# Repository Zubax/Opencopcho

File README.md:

# Opencopcho

Open hardware shield for the [NUCLEO-H743ZI](https://www.st.com/en/evaluation-tools/nucleo-h743zi.html) board
for UAVCAN development.

Ask questions on the [UAVCAN forum](https://forum.uavcan.org) or [Zubax forum](https://forum.zubax.com).

Opencopcho is pronounced like [*open-cop-chow*](https://translate.google.com/#en/en/opencopcho).

## Design

The shield features two CAN FD interfaces with three pairs of standard UAVCAN-compatible connectors
(two connectors per interface).

The shield can be assembled in two configurations: **full** and **micro**.
The full configuration provides three types of connectors defined by the UAVCAN specification:

* UAVCAN Micro type (JST GH 4-pin)
* UAVCAN D-Subminiature (D-Sub DE9, de-facto industry-standard CAN connector)
* 2.54mm pin headers for connection to panel-mounted UAVCAN M8 connectors
(M8 5-pin B-coded connector, also used in CANopen)

The micro configuration has only the UAVCAN Micro connectors populated.
In this configuration, Opencopcho can be used with other shields stacked on top of it.

Full configuration                  | Micro configuration
------------------------------------|------------------------------------------
     | 
  |

A 3D render is available here: <https://a360.co/2R1n94m>.

## License

This work is licensed under a
[Creative Commons Attribution 4.0 International License](http://creativecommons.org/licenses/by/4.0/).

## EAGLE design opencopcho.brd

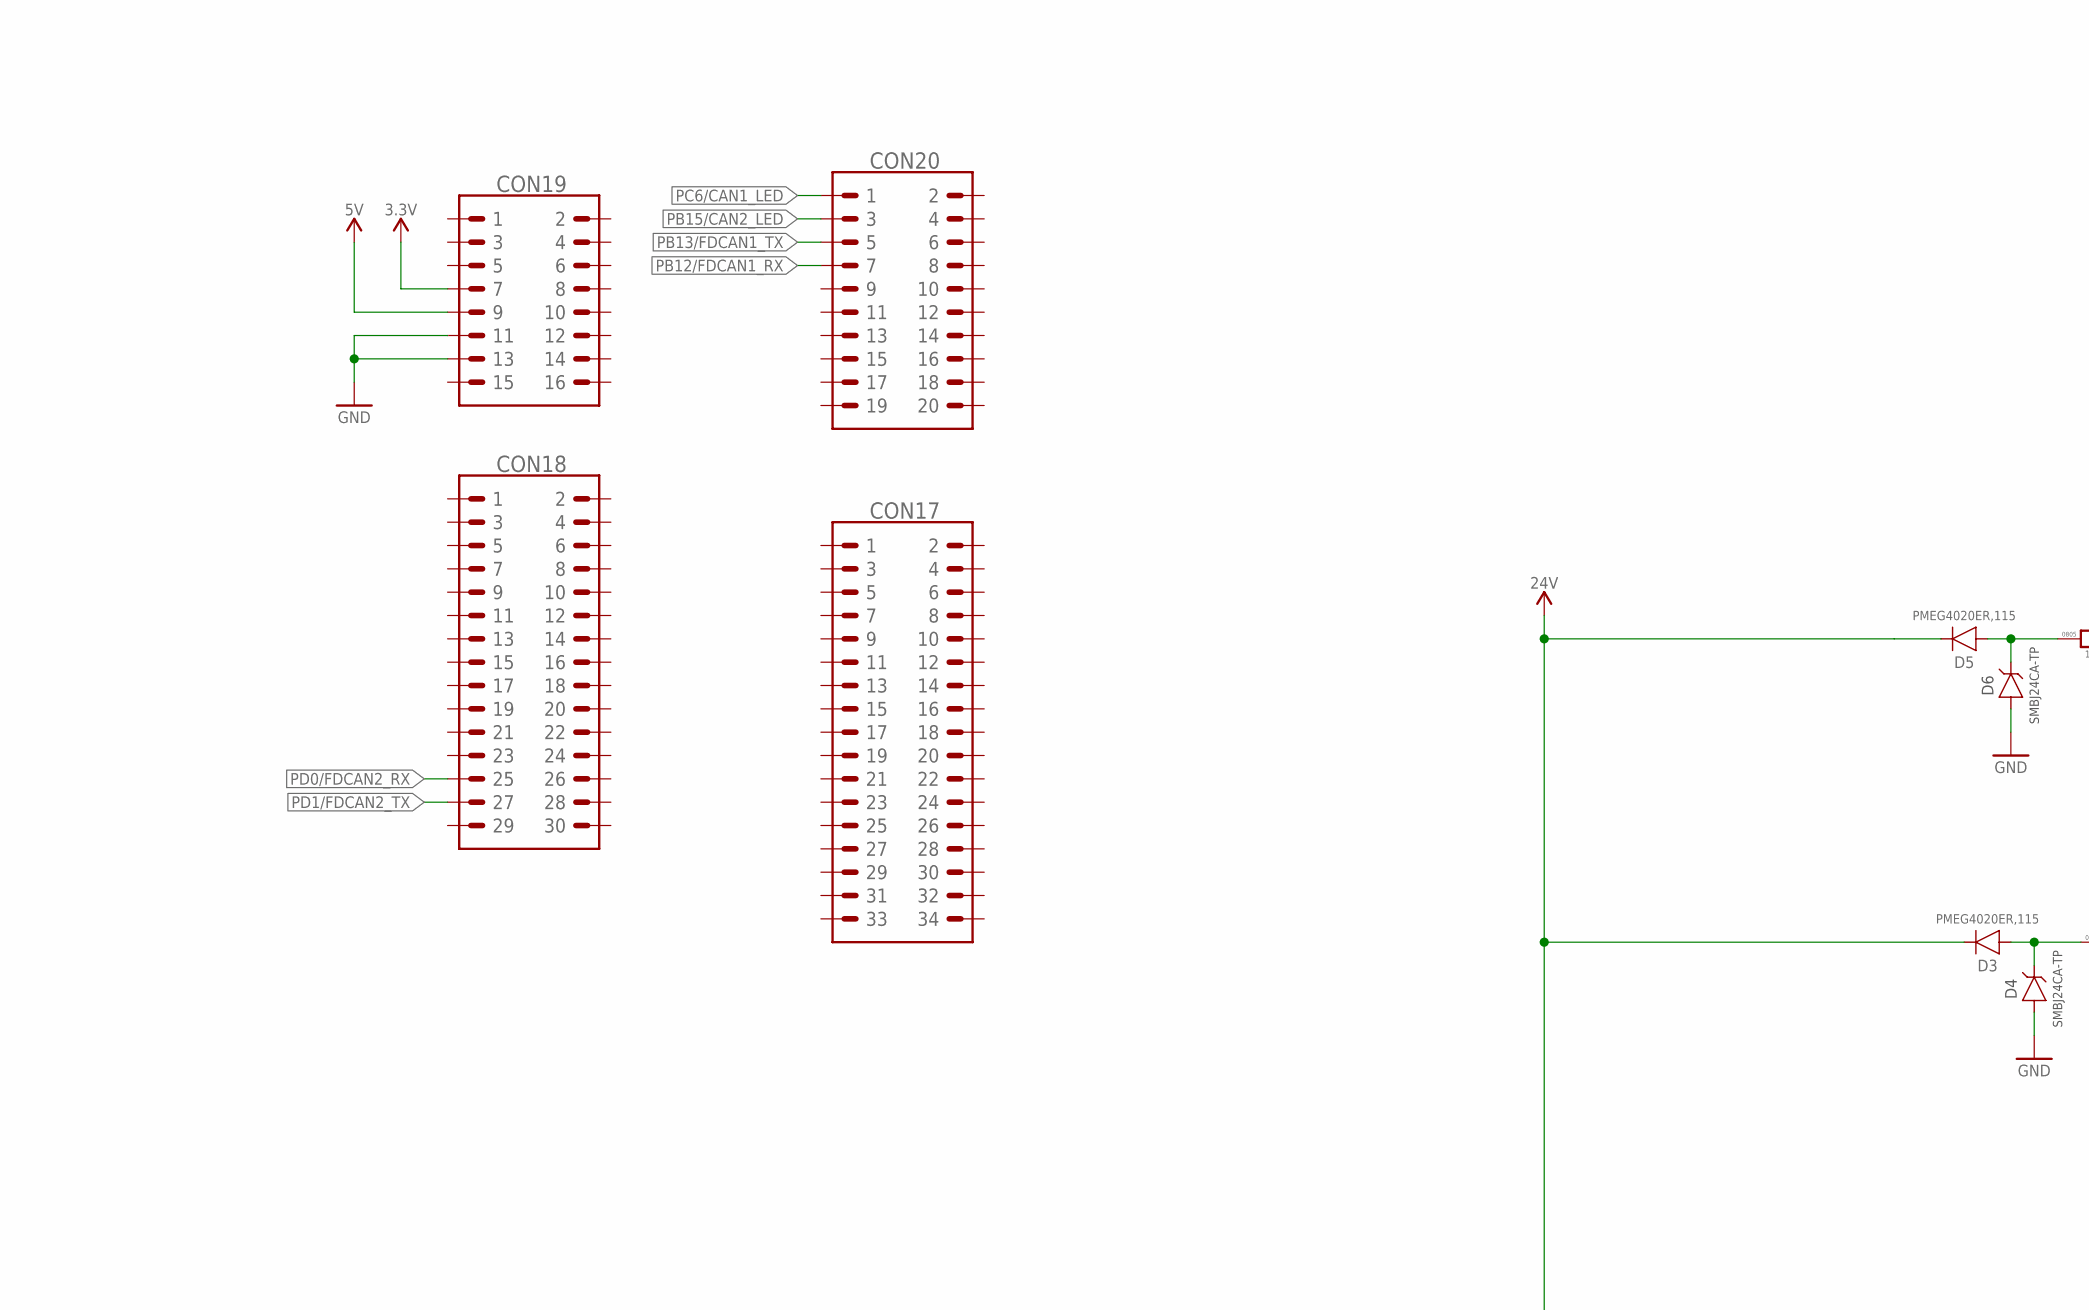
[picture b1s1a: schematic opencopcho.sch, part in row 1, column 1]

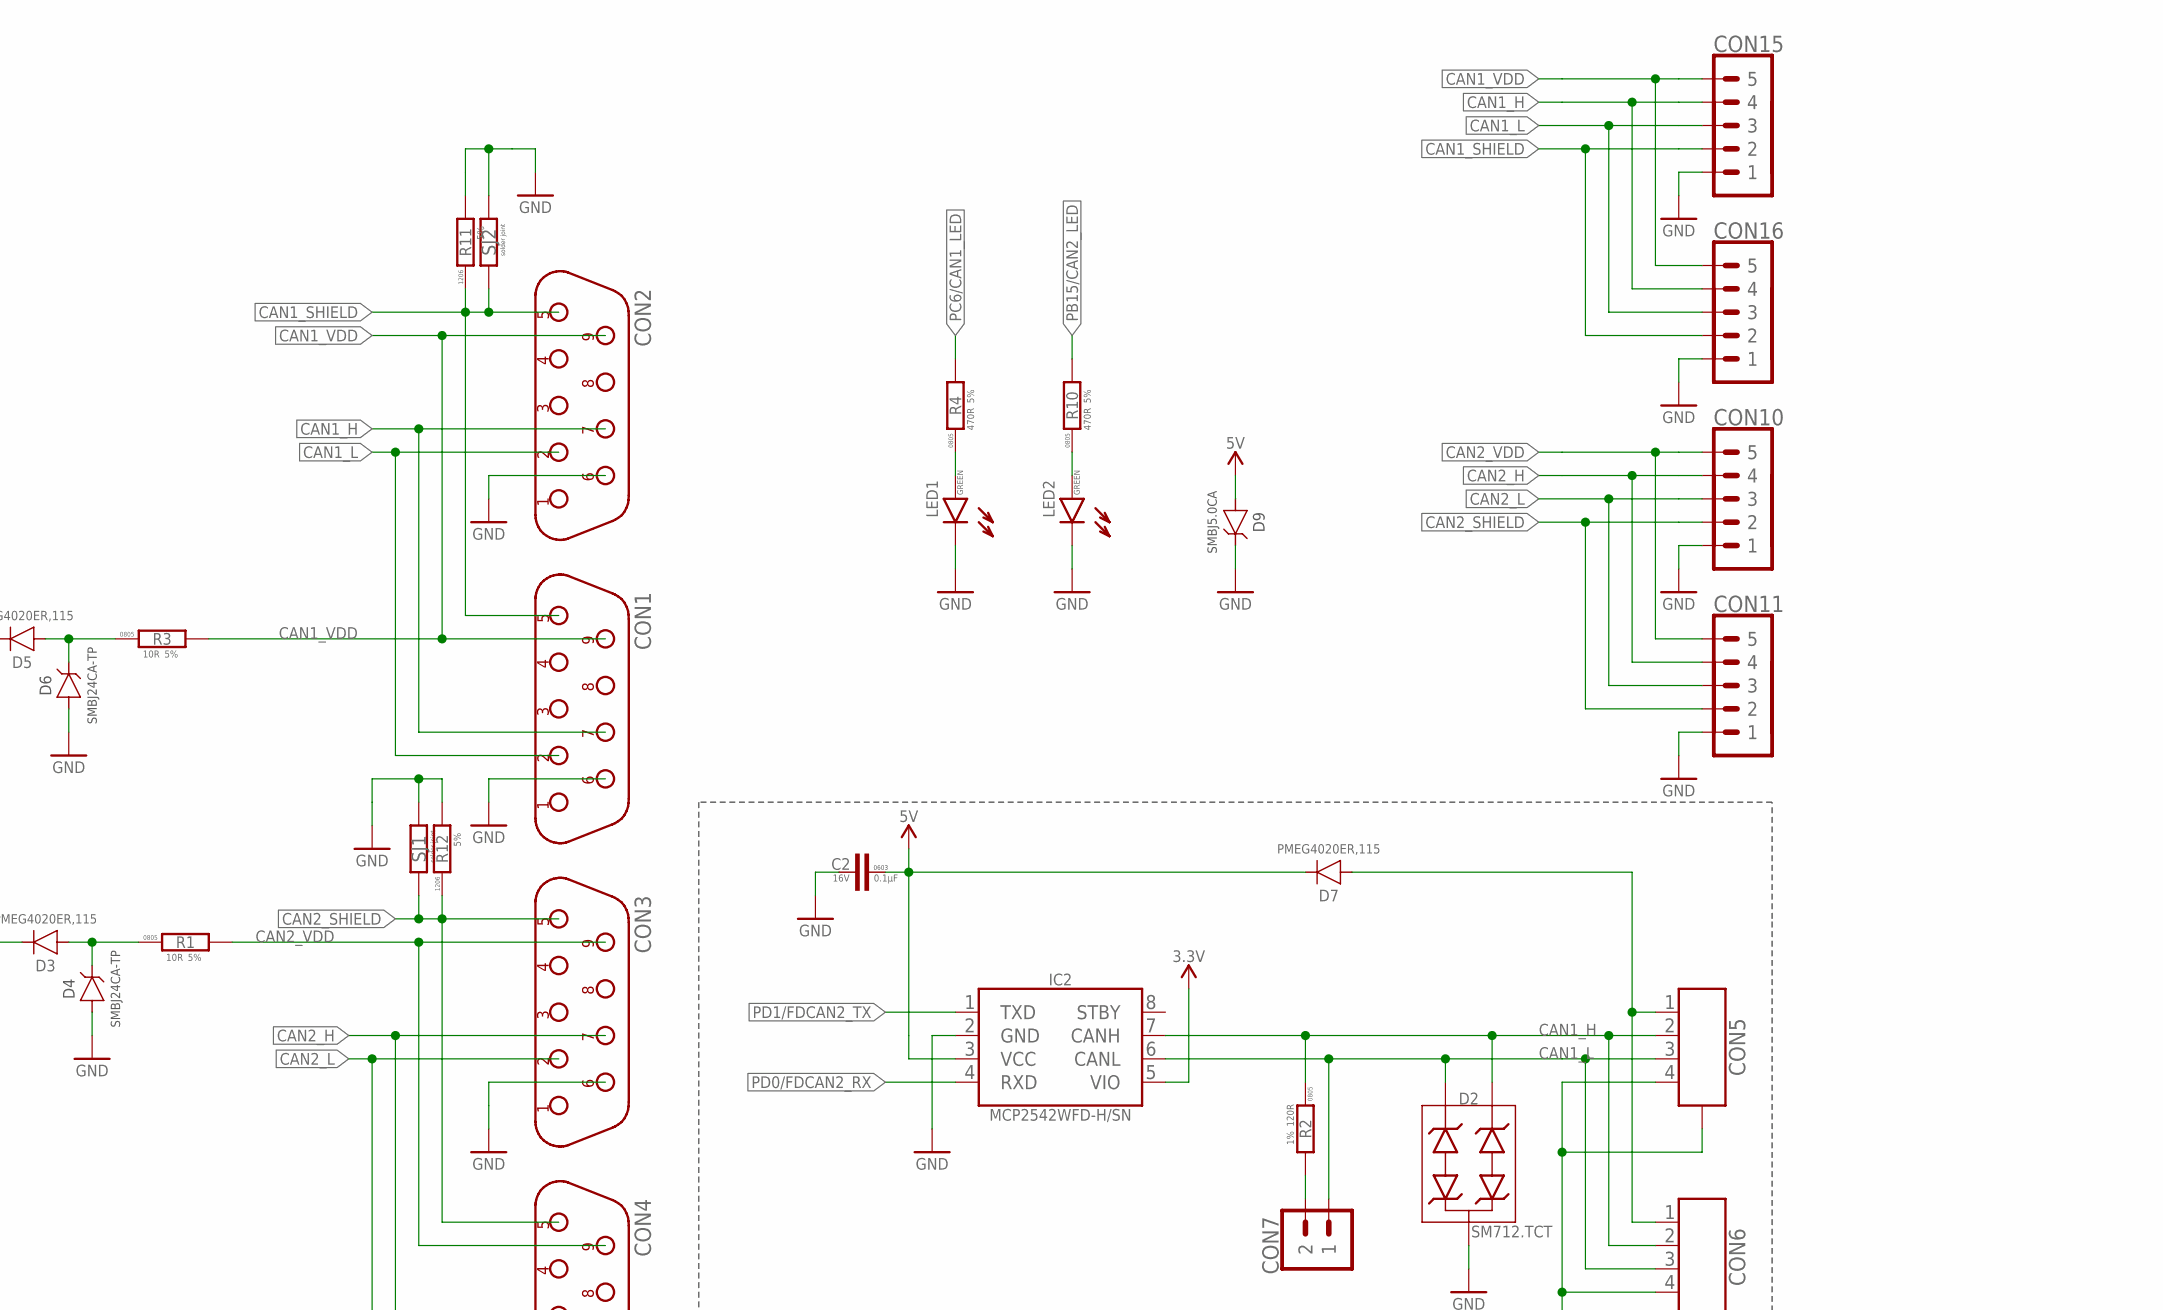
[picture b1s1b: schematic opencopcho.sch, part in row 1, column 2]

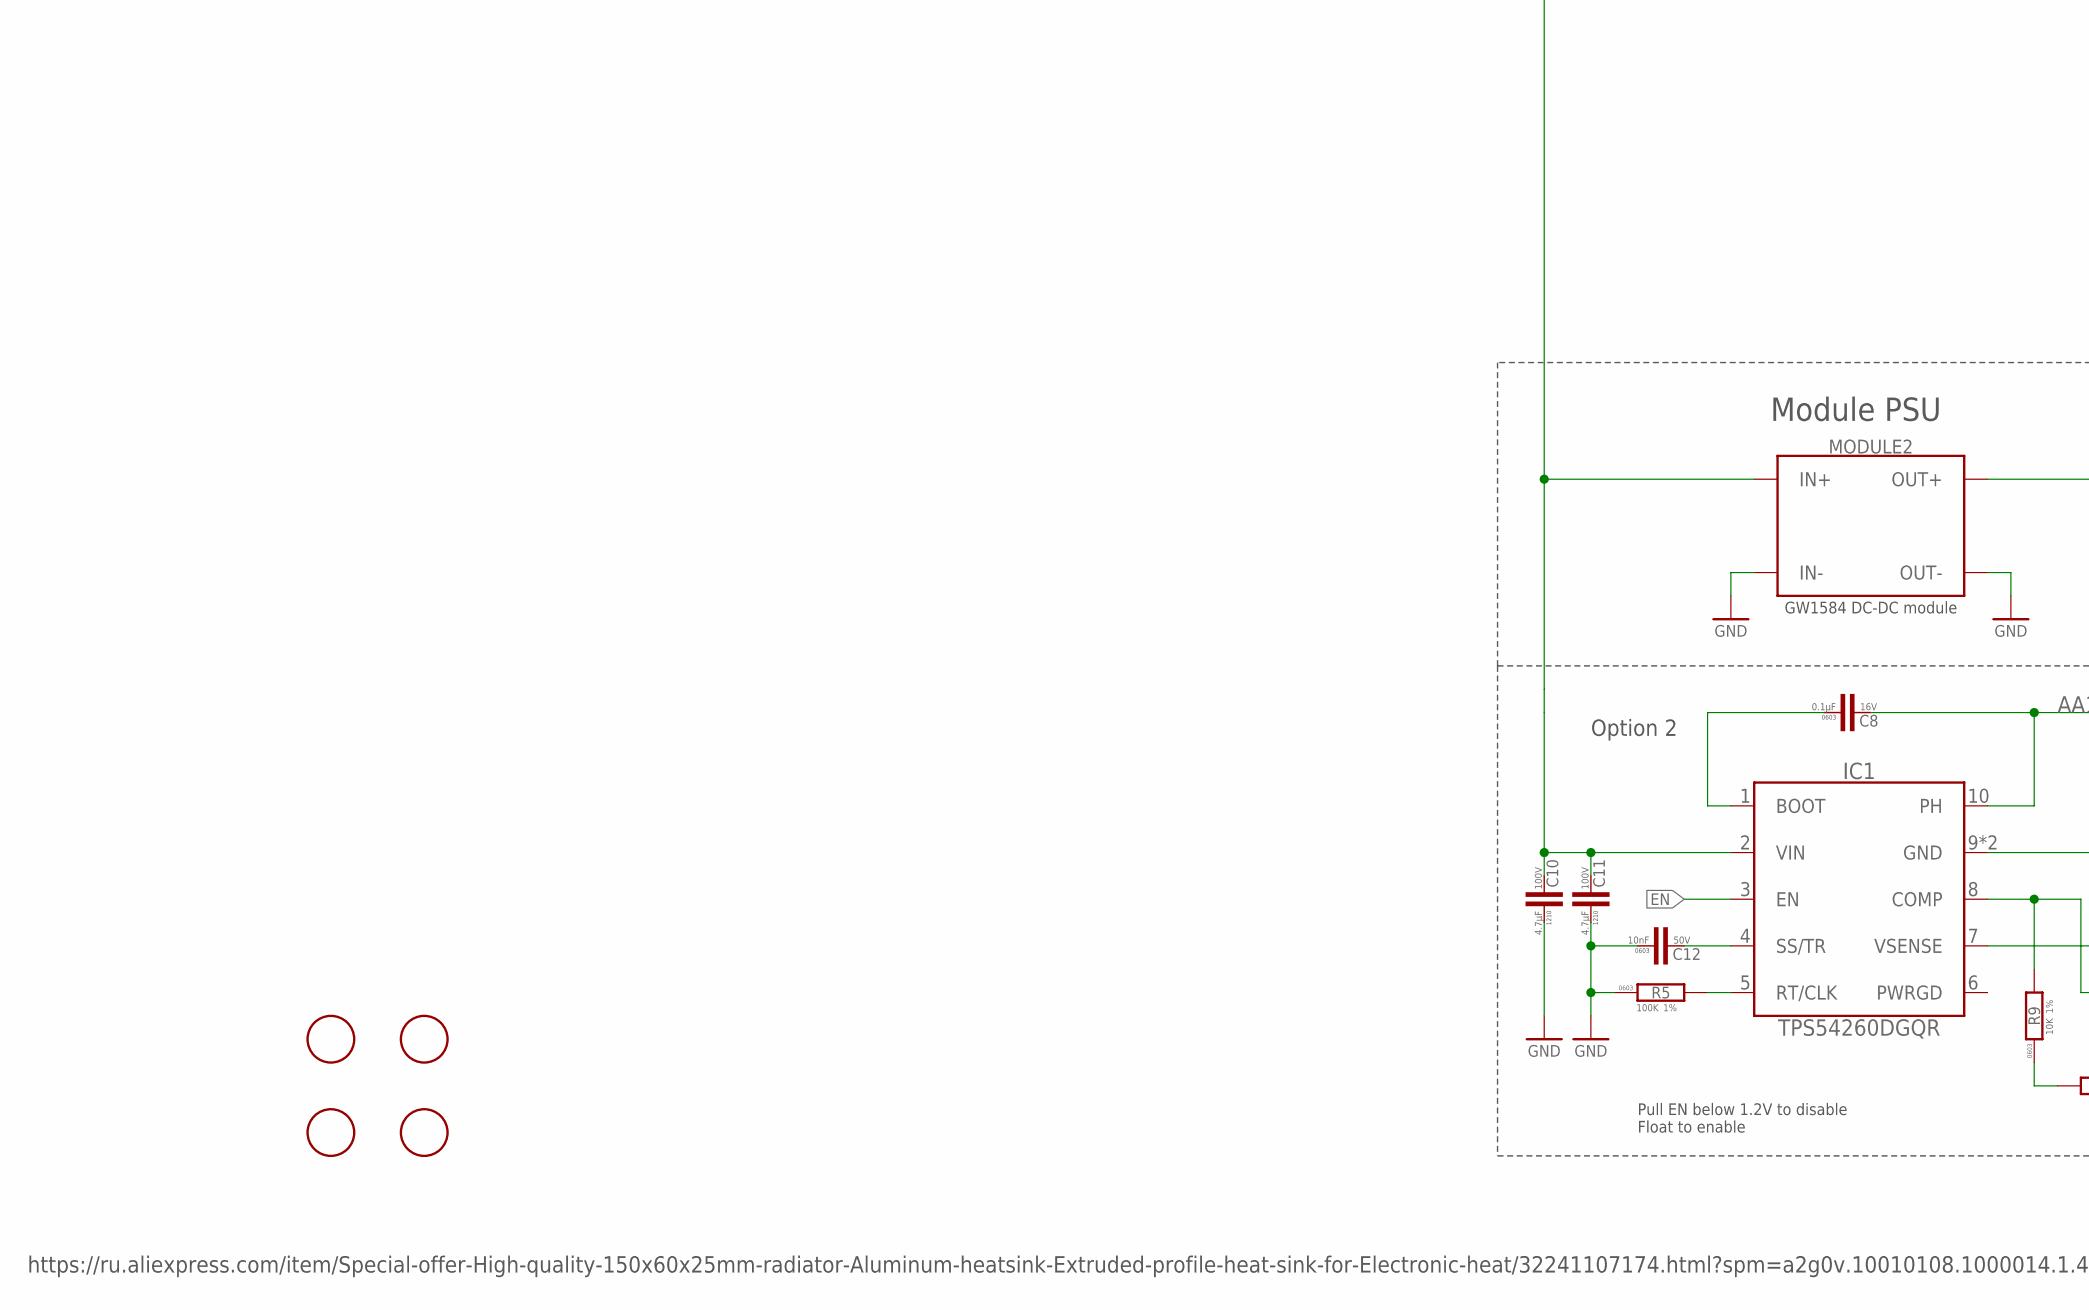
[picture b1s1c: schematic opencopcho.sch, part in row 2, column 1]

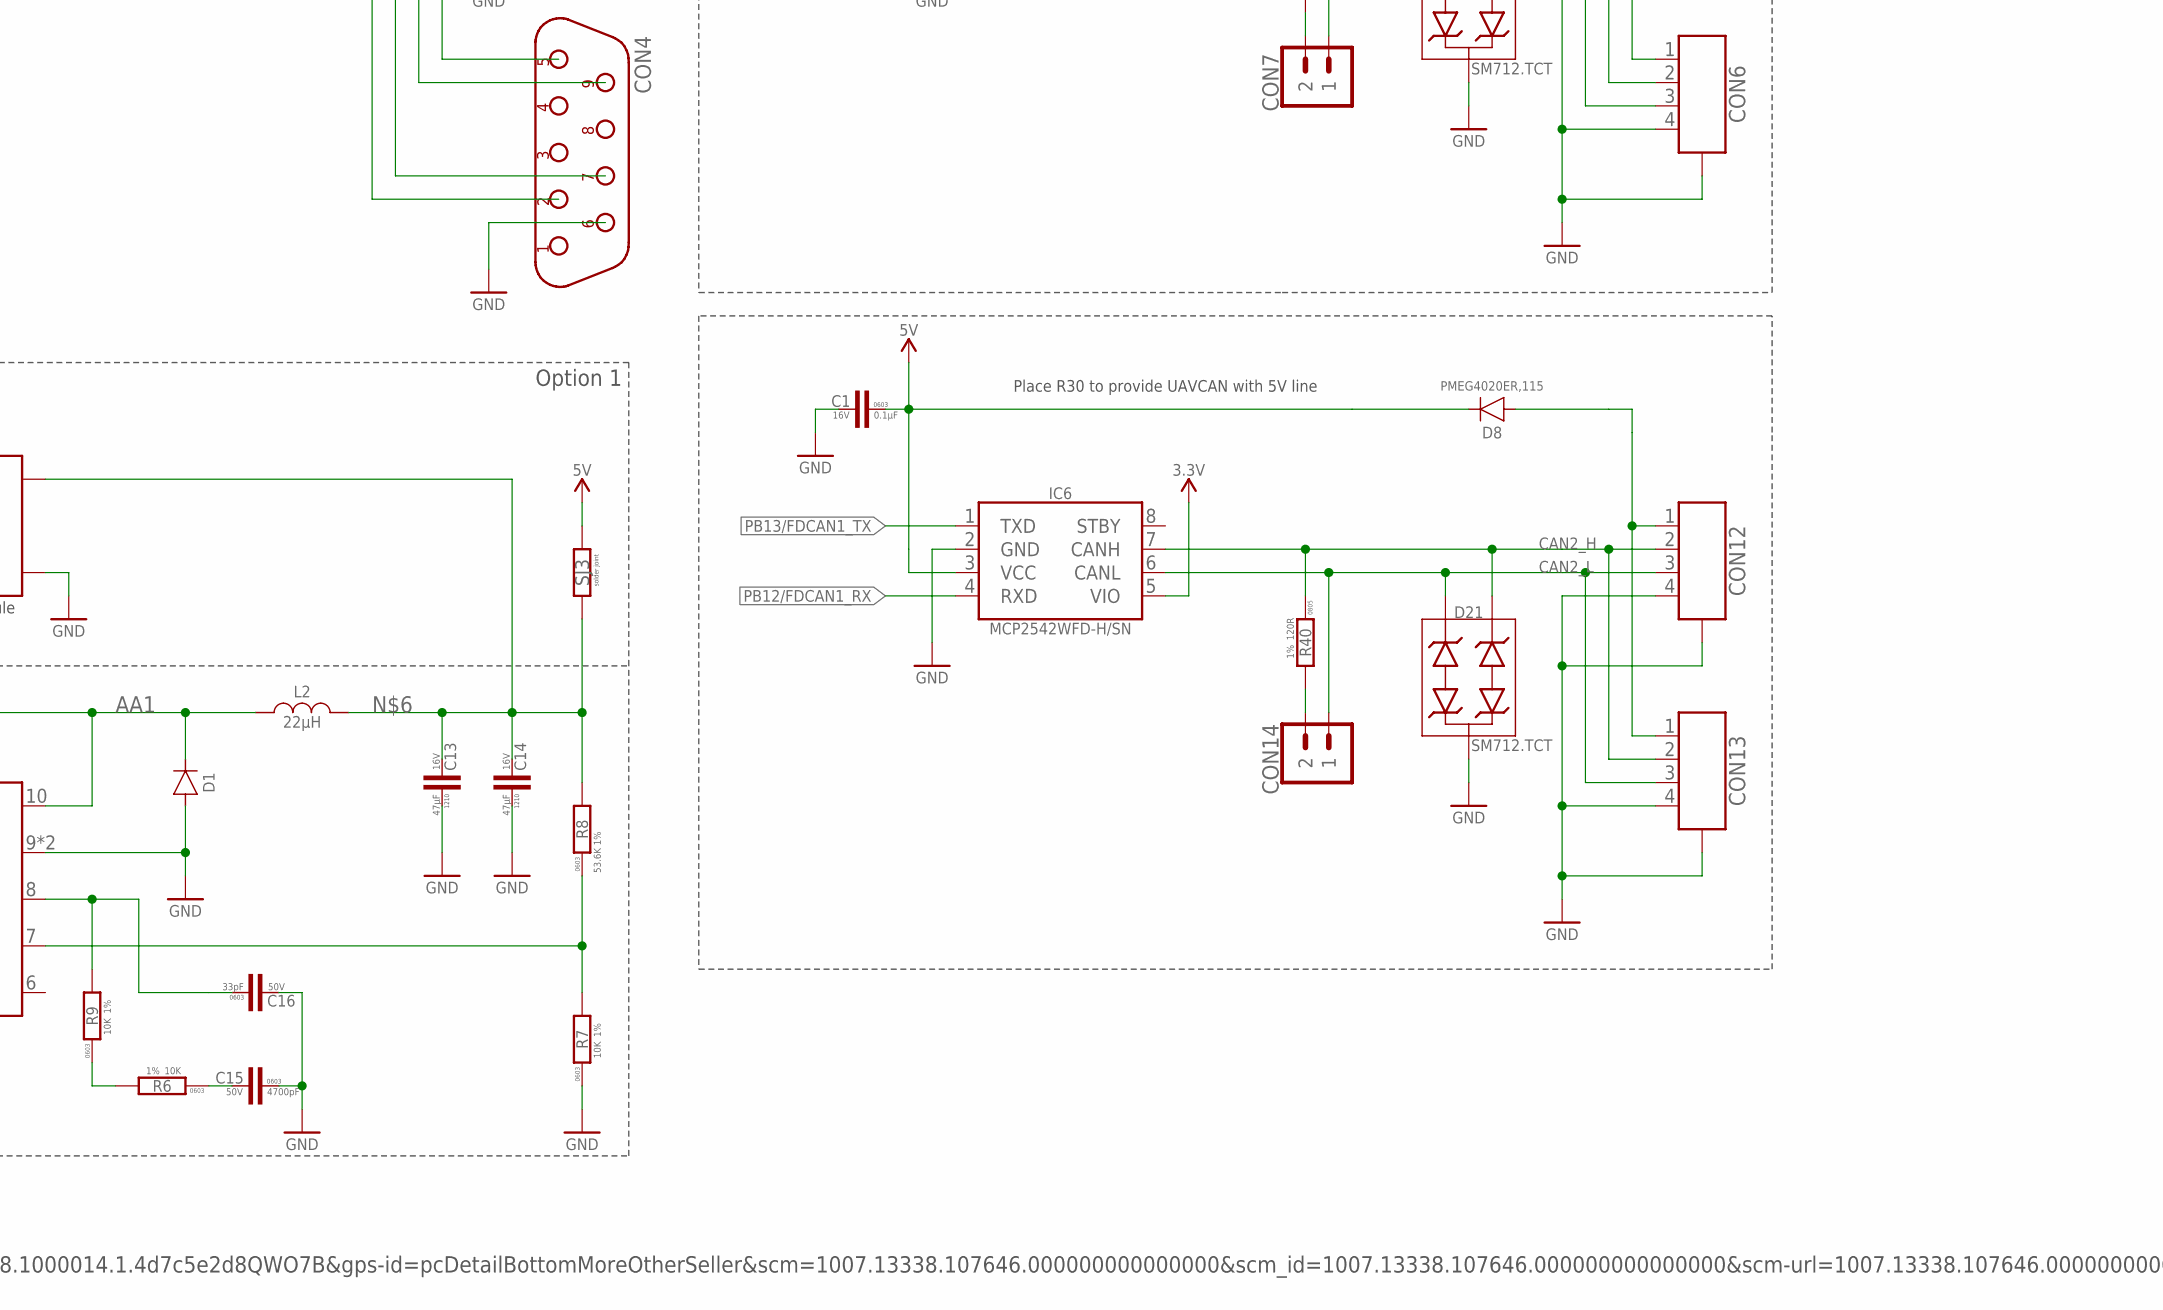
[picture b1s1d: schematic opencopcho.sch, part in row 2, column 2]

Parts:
C1, C2, C8: 0.1µF; C0603
C10, C11: 4.7µF; C1210
C12: 10nF; C0603
C13, C14: 47µF; C1210
C15: 4700pF; C0603
C16: 33pF; C0603
CON1, CON2, CON3, CON4: DB9-M; D-09M
CON5, CON6, CON12, CON13: CON-4P-JST_GH-RA; JST_GH-4P-RA
CON7, CON14: PINHEAD_1X02-2.54; 1X02-PTH-2.54
CON10, CON11, CON15, CON16: PINHEAD_1X05-2.54-KEY; 1X05-PTH-2.54-KEY
CON17: PINHEAD_2X17-TH-FEMALE-LONG; 2X17-PTH-2.54-FEMALE-LONG_PINS
CON18: PINHEAD_2X15-2.54-FEMALE-LONG; 2X15-PTH-2.54-FEMALE-LONG-PINS
CON19: PINHEAD_2X08-TH-FEMALE-LONG; 2X08-PTH-2.54-FEMALE-LONG-PINS
CON20: PINHEAD_2X10-2.54-TH-FEMALE-LONG; 2X10-PTH-2.54-FEMALE-LONG-PINS
D1: B360B; DO-214AA(SMB); DIGIKEY# B360B-FDICT-ND
D2, D21: SM712; SOT23B-3
D3, D5, D7, D8: PMEG4020; SOD123W
D4, D6: SMBJ24CA-SMB; DO-214AA(SMB)
D9: SMBJ5.0CA-SMB; DO-214AA(SMB)
IC1: TPS54260; MSOP10
IC2, IC6: MCP2542WFD; SOIC8-3.9
L2: 22µH; SRP6540; DIGIKEY# SRP6540-4R7MCT-ND
LED1, LED2: LED-0805; LED0805
MODULE2: GW1584_MODULE
R1, R3: 10R; R0805
R2, R40: 120R; R0805
R4, R10: 470R; R0805
R5: 100K; R0603
R6, R7, R9: 10K; R0603
R8: 53.6K 1%; R0603; DIGIKEY# 311-53.6KHRCT-ND
R11, R12: R-5%-1206; R1206
SJ1, SJ2, SJ3: SOLDER_JOINT; RES_0
U$5, U$6, U$7, U$11: FIDUCIALMOUNT; FIDUCIA-MOUNT

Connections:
AA1: C8.P$2 (2), D1.C, IC1.10 (PH), L2.1
CAN1_H: CON1.7, CON2.7, CON5.2, CON6.2, CON15.4, CON16.4, D2.1 (C3), IC2.7 (CANH), R2.1
CAN1_L: CON1.2, CON2.2, CON5.3, CON6.3, CON7.1, CON15.3, CON16.3, D2.2 (C2), IC2.6 (CANL)
CAN1_SHIELD: CON1.5, CON2.5, CON15.2, CON16.2, R11.P$1 (1), SJ2.1
CAN1_VDD: CON1.9, CON2.9, CON15.5, CON16.5, R3.2
CAN2_H: CON3.7, CON4.7, CON10.4, CON11.4, CON12.2, CON13.2, D21.1 (C3), IC6.7 (CANH), R40.1
CAN2_L: CON3.2, CON4.2, CON10.3, CON11.3, CON12.3, CON13.3, CON14.1, D21.2 (C2), IC6.6 (CANL)
CAN2_SHIELD: CON3.5, CON4.5, CON10.2, CON11.2, R12.P$1 (1), SJ1.1
CAN2_VDD: CON3.9, CON4.9, CON10.5, CON11.5, R1.2
EN: IC1.3 (EN)
FB1: IC1.7 (VSENSE), R7.P$2 (2), R8.1
GND: C1.P$2 (2), C2.P$2 (2), C10.1, C11.1, C12.P$1 (1), C13.1, C14.1, C15.P$1 (1), C16.P$2 (2), CON1.6, CON2.6, CON3.6, CON4.6, CON5.4, CON5.M$0 (GND), CON5.M$1 (GND), CON6.4, CON6.M$0 (GND), CON6.M$1 (GND), CON10.1, CON11.1, CON12.4, CON12.M$0 (GND), CON12.M$1 (GND), CON13.4, CON13.M$0 (GND), CON13.M$1 (GND), CON15.1, CON16.1, CON19.11, CON19.13, D1.A, D2.3, D4.A, D6.A, D9.C, D21.3, IC1.9 (GND), IC1.TPAD (GND), IC2.2 (GND), IC6.2 (GND), LED1.C, LED2.C, MODULE2.IN-@1 (IN-), MODULE2.IN-@2 (IN-), MODULE2.OUT-@1 (OUT-), MODULE2.OUT-@2 (OUT-), R5.P$1 (1), R7.P$1 (1), R11.P$2 (2), R12.P$2 (2), SJ1.2, SJ2.2
unnamed: C8.P$1 (1), IC1.1 (BOOT)
unnamed: LED1.A, R4.1
unnamed: CON12.1, CON13.1, D8.A
unnamed: C12.P$2 (2), IC1.4 (SS/TR)
unnamed: CON7.2, R2.2
unnamed: C13.2, C14.2, L2.2, MODULE2.OUT+@1 (OUT+), MODULE2.OUT+@2 (OUT+), R8.2, SJ3.1
unnamed: LED2.A, R10.1
unnamed: CON5.1, CON6.1, D7.A
unnamed: IC1.5 (RT/CLK), R5.P$2 (2)
unnamed: C16.P$1 (1), IC1.8 (COMP), R9.P$2 (2)
unnamed: C15.P$2 (2), R6.P$1 (1)
unnamed: R6.P$2 (2), R9.P$1 (1)
unnamed: D5.A, D6.C, R3.1
unnamed: D3.A, D4.C, R1.1
unnamed: CON14.2, R40.2
PB12/FDCAN1_RX: CON20.7, IC6.4 (RXD)
PB13/FDCAN1_TX: CON20.5, IC6.1 (TXD)
PB15/CAN2_LED: CON20.3, R10.2
PC6/CAN1_LED: CON20.1, R4.2
PD0/FDCAN2_RX: CON18.25, IC2.4 (RXD)
PD1/FDCAN2_TX: CON18.27, IC2.1 (TXD)
VDD_3V3: CON19.7, IC2.5 (VIO), IC6.5 (VIO)
VDD_5V: C1.P$1 (1), C2.P$1 (1), CON19.9, D7.C, D8.C, D9.A, IC2.3 (VCC), IC6.3 (VCC), SJ3.2
VDD_24V: C10.2, C11.2, D3.C, D5.C, IC1.2 (VIN), MODULE2.IN+@1 (IN+), MODULE2.IN+@2 (IN+)

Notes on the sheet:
Pull EN below 1.2V to disable Float to enable
Module PSU
Option 1
Option 2
Place R30 to provide UAVCAN with 5V line
https://ru.aliexpress.com/item/Special-offer-High-quality-150x60x25mm-radiator-Aluminum-heatsink-Extruded-profile-heat-sink-for-Electronic-heat/32241107174.html?spm=a2g0v.10010108.1000014.1.4d7c5e2d8QWO7B&gps-id=pcDetailBottomMoreOtherSeller&scm=1007.13338.107646.000000000000000&scm_id=1007.13338.1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

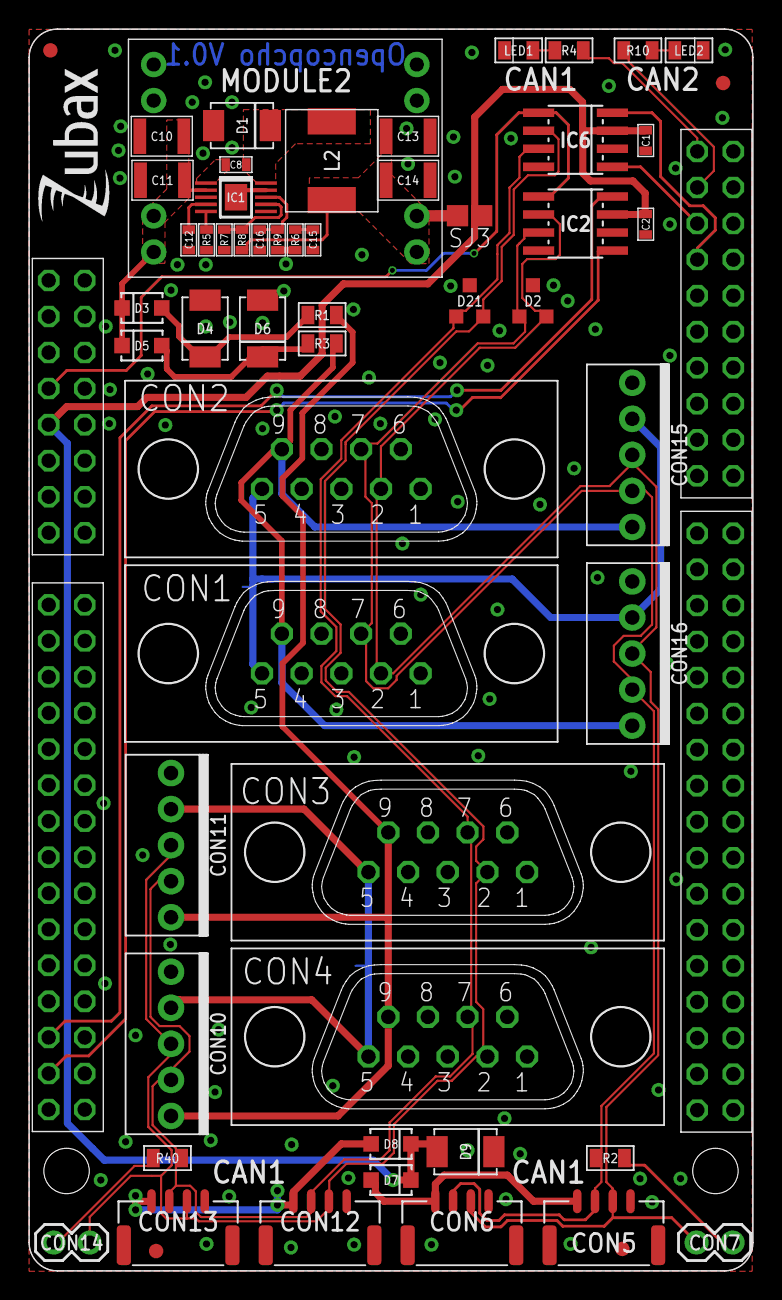
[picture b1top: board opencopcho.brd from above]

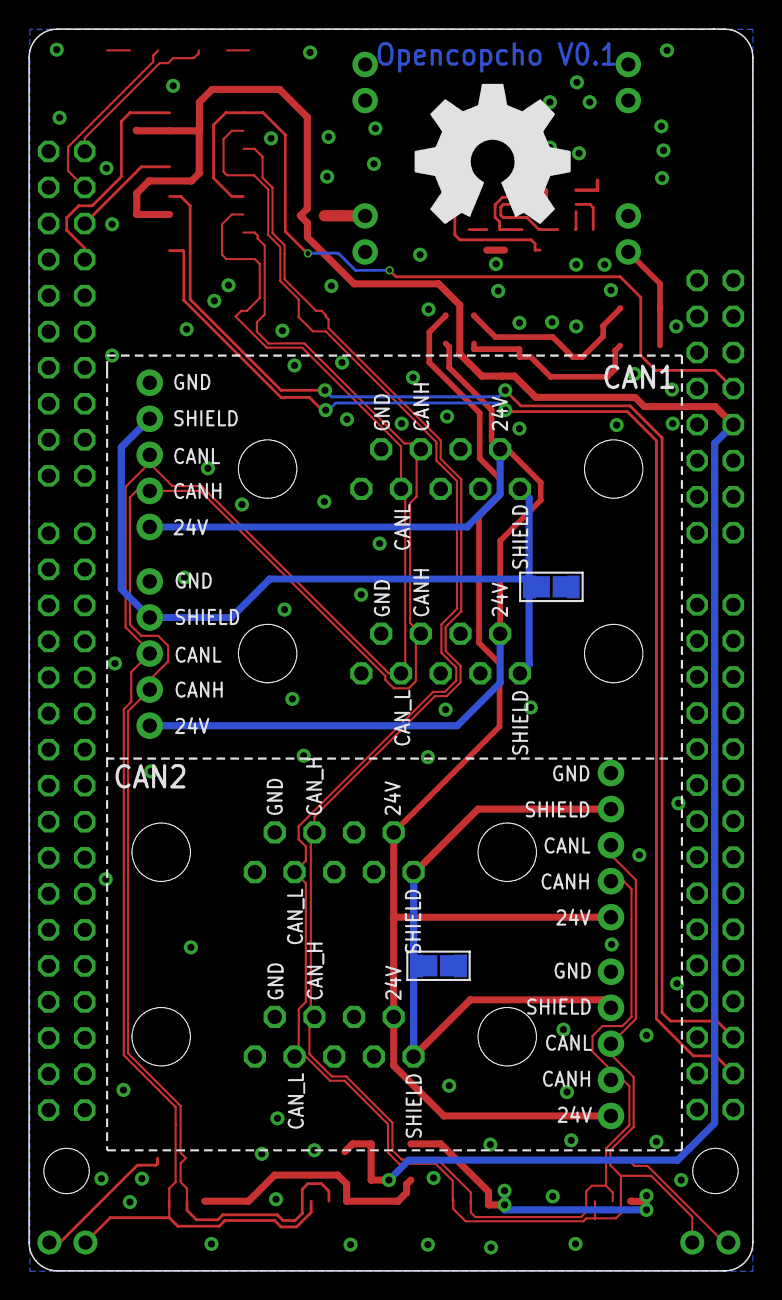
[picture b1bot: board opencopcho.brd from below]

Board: 2 copper layers, 51.0 x 87.5 mm, 67 parts (5 on the bottom side), 35 nets.

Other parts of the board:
U$1: ZUBAX_LOGO_5X10
U$4: OSHW-10.5X11.5

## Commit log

2018-11-19 initial import
2018-11-20 proper gitignore
2018-11-20 some updates
2018-11-22 opencopcho is basically done
2018-11-23 fiducials
2018-11-23 basic assembly variant
2018-11-23 temporary BOM link
2018-11-23 silk updates
2018-11-23 production docs update
2018-11-23 3d view update
2018-11-28 README update
2018-11-28 Resized pics
2018-11-28 Table
2018-11-28 Table x2
